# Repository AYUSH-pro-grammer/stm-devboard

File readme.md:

# STM32H573 Development Board

A custom development board based on the STM32H573RIT6 microcontroller, created in KiCad that serves the purpose of learning about the hardware design, PCB layout, power supply and embedded systems.

## Features

### Core components
- Power supply: The board is powered through the USB-C connector. 3.3 V is supplied by the LD1117S33TR regulator.
- Microcontroller: The STM32H573RIT6 processes the firmware code and communicates with peripherals.
- Clock source: 8 MHz crystal serves as an external clock for the microcontroller.
- Pushbuttons and resistors: Used to reset and enter the boot mode.
- USB Protection: USBLC6-2P6 is used for ESD protection of the USB lines.
- Programming and debugging: SWD connector is used for flashing firmware and debugging.
- Headers: Expose some of the pins for expansion.

## The reason behind making this

This board was made by me in order to gain knowledge about how to make an STM32 development board on my own rather than relying on readymade boards available out there.

## Flashing and use

The board is equipped with a USB-C port thus it can be connected to a PC. In case that USB DFU bootloading is set up properly, you may flash the firmware directly via USB and no ST-LINK debugger will be required.

Otherwise, it is still possible to program and debug the board via ST-LINK through the SWD connector.

After flashing the firmware, reboot the board and get started playing around with GPIOs!

## Assembly

The PCB assembly will be done by manually soldering all the parts to the PCB.

## Images

### 3D PCB View — Front

### 3D PCB View — Back

### Schematic

### PCB Routing

## Hardware Design

I have used KiCad to design both the schematic and the PCB.

- `kicad/` — Schematic and PCB design files
- `images/` — Images of PCB rendering, schematic and routing
- `gerber-files/` — PCB manufacturing files
- `bom.csv` — Bill of materials with links to parts
- `grb.zip` — Gerber archive if present

## Bill of Materials

The bill of materials with links to parts is listed in [`bom.csv`](bom.csv)

## BOM

| Qty | Component | Selected Part | Supplier | Link | MOQ | Unit Price (USD) | Order Cost (USD) |
| -------: | ------------- | ----------------- | ------------ | -------- | -------: | --------------------: | -------------------: |
| 100 | 30 pF Capacitor, 0603 C0G | TCC0603COG300J500CT | LCSC | [Link](https://www.lcsc.com/product-detail/C376782.html) | 100 | $0.0042 | $0.42 |
| 20 | Red LED, 0603 | DY-0603SRC-L-SMG | LCSC | [Link](https://www.lcsc.com/product-detail/C524047.html) | 20 | $0.0252 | $0.50 |
| 20 | Schottky Diode, 1N5819 DO-41 | 1N5819 | LCSC | [Link](https://www.lcsc.com/product-detail/C2474.html) | 20 | $0.0367 | $0.73 |
| 10 | 2.2 µF Capacitor, 0805 X7R | CC0805KKX7R7BB225 | LCSC | [Link](https://www.lcsc.com/product-detail/C107128.html) | 10 | $0.0601 | $0.60 |
| 20 | 1 µF Capacitor, 0805 X7R | 0805B105K160CT | LCSC | [Link](https://www.lcsc.com/product-detail/C396719.html) | 20 | $0.0457 | $0.91 |
| 10 | 4.7 µF Capacitor, 0805 X7R | CC0805MKX7R8BB475 | LCSC | [Link](https://www.lcsc.com/product-detail/C5185457.html) | 10 | $0.0717 | $0.72 |
| 50 | 10 pF Capacitor, 0603 NP0 | AC0603JRNPO9BN100 | LCSC | [Link](https://www.lcsc.com/product-detail/C277527.html) | 50 | $0.0106 | $0.53 |
| 5 | 10 µF Capacitor, 0805 X7R | TCC0805X7R106K100FT | LCSC | [Link](https://www.lcsc.com/product-detail/C380346.html) | 5 | $0.0918 | $0.46 |
| 20 | 100 nF Capacitor, 0603 X7R | CC0603JRX7R9BB104 | LCSC | [Link](https://www.lcsc.com/product-detail/C91183.html) | 20 | $0.0209 | $0.42 |
| 50 | Green LED, 0603 | KT-0603G | LCSC | [Link](https://www.lcsc.com/product-detail/C12624.html) | 50 | $0.0124 | $0.62 |
| 50 | Blue LED, 0603 — Backordered | KT-0603B | LCSC | [Link](https://www.lcsc.com/product-detail/C2288.html) | 50 | $0.0104 | $0.52 |
| 1 | USB-C USB 2.0 Connector — Backordered | USB4105-GF-A-060 | LCSC | [Link](https://www.lcsc.com/product-detail/C3025063.html) | 1 | $1.4727 | $1.47 |
| 20 | 1×4 Pin Header, 2.54 mm | PZ254V-11-04P | LCSC | [Link](https://www.lcsc.com/product-detail/C2691448.html) | 20 | $0.0263 | $0.53 |
| 10 | 1×6 Pin Header, 2.54 mm | 2.54-1x6P | LCSC | [Link](https://www.lcsc.com/product-detail/C37208.html) | 10 | $0.0419 | $0.42 |
| 5 | N-Channel MOSFET, SOT-523 | DMG1012T-7 | LCSC | [Link](https://www.lcsc.com/product-detail/C20512.html) | 5 | $0.1019 | $0.51 |
| 20 | 10 kΩ Resistor, 0603 | MCT06030C1002FP500 | LCSC | [Link](https://www.lcsc.com/product-detail/C161803.html) | 20 | $0.0377 | $0.75 |
| 10 | 5.1 kΩ Resistor, 0603 | HoAR0603-1/10W-5.1KR-0.1%-TCR25 | LCSC | [Link](https://www.lcsc.com/product-detail/C5123587.html) | 10 | $0.0728 | $0.73 |
| 20 | 1.4 kΩ Resistor, 0603 | RT0603BRD071K4L | LCSC | [Link](https://www.lcsc.com/product-detail/C705740.html) | 20 | $0.0596 | $1.19 |
| 10 | 1.1 kΩ Resistor, 0603 | RT0603BRD071K1L | LCSC | [Link](https://www.lcsc.com/product-detail/C705736.html) | 10 | $0.0508 | $0.51 |
| 1 | 160 Ω Resistor, 0603 — Backordered | ERJP03F1600V | LCSC | [Link](https://www.lcsc.com/product-detail/C543226.html) | 1 | $0.0598 | $0.06 |
| 1 | 221 Ω Resistor, 0603 — Backordered | ERJ-S03F2210V | LCSC | [Link](https://www.lcsc.com/product-detail/C2113629.html) | 1 | $0.0270 | $0.03 |
| 5 | USB ESD Protection, SOT-666 — Backordered | USBLC6-2P6 | LCSC | [Link](https://www.lcsc.com/product-detail/C15999.html) | 5 | $0.2491 | $1.25 |
| 5 | 3.3 V LDO Regulator, SOT-223 | LD1117S33TR | LCSC | [Link](https://www.lcsc.com/product-detail/C86781.html) | 5 | $0.2467 | $1.23 |
| 5 | 8 MHz Crystal, 18 pF, SMD3225 | 0132M4-8.000F18DTNL | LCSC | [Link](https://www.lcsc.com/product-detail/C51949868.html) | 5 | $0.1920 | $0.96 |
| 1 | STM32H573RIT6 Microcontroller — Backordered | STM32H573RIT6 | LCSC | [Link](https://www.lcsc.com/product-detail/C22371377.html) | 1 | $9.9787 | $9.98 |
| 50 | 6×6 mm Tactile Switch | SH-6X6X5H-STM | LCSC | [Link](https://www.lcsc.com/product-detail/C22383475.html) | 50 | $0.0115 | $0.58 |
| 1 | PCB Fabrication | Custom STM32H573 PCB | JLCPCB | [JLCPCB](https://jlcpcb.com/) | 1 | $8.00 | $8.00 |
| | Total cost | | | | | | $34.63 |

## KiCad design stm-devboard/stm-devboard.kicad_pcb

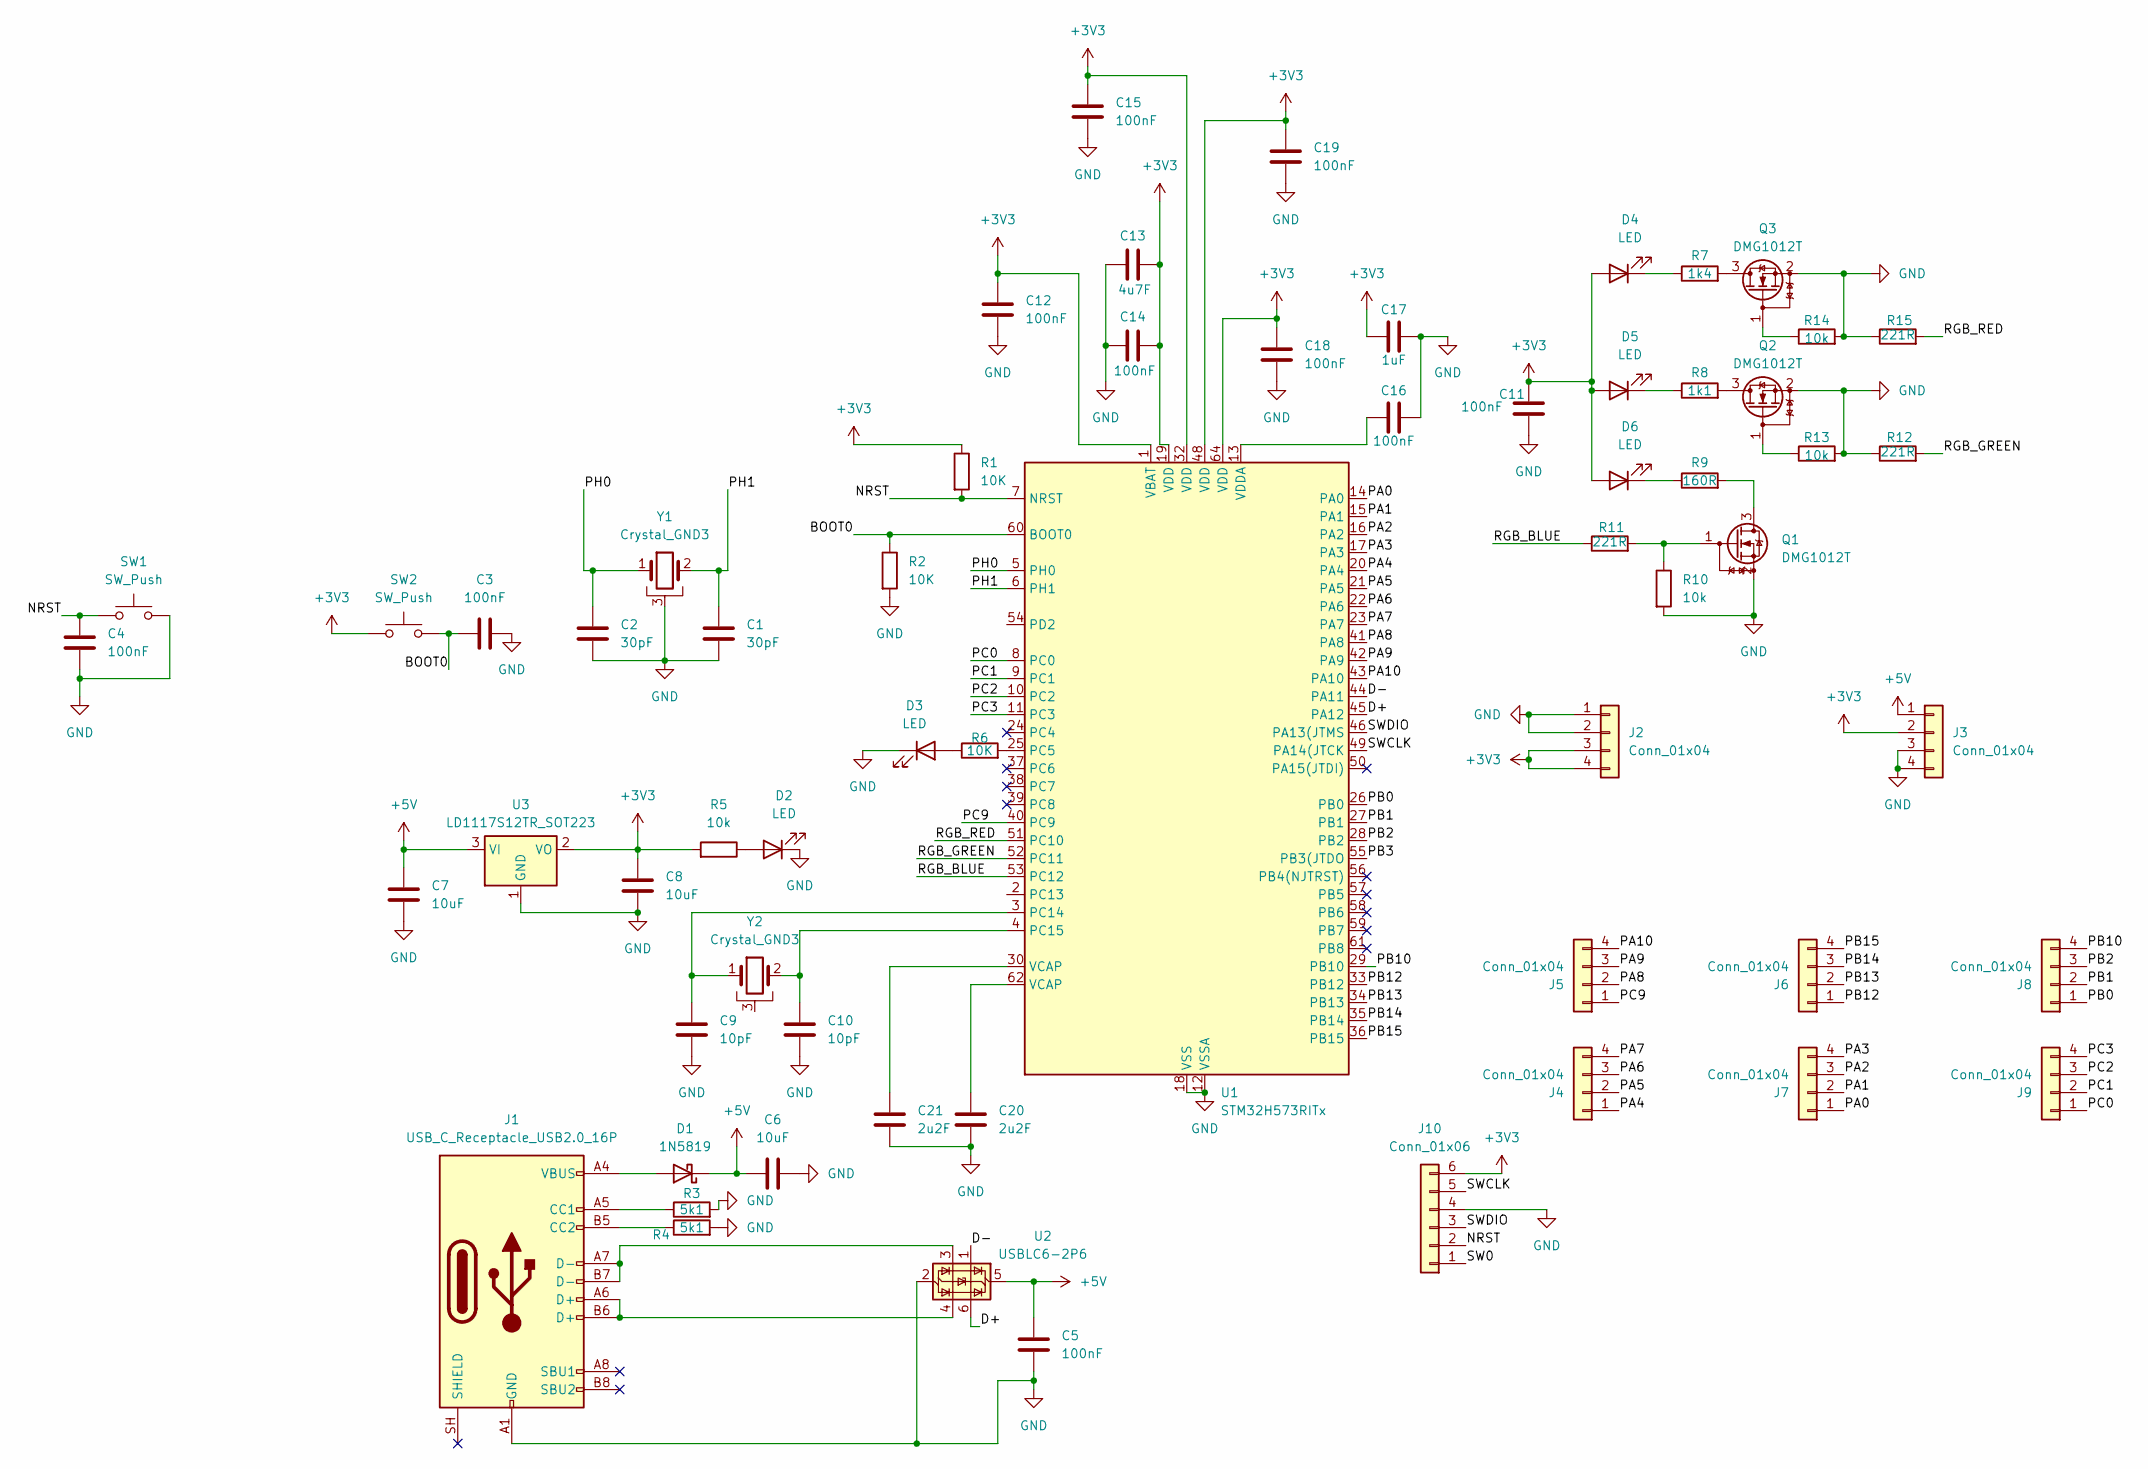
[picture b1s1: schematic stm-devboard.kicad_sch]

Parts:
C1, C2: 30pF; C_0603_1608Metric
C3, C4, C5, C11, C12, C14, C15, C16, C18, C19: 100nF; C_0603_1608Metric
C6, C7, C8: 10uF; C_0805_2012Metric
C9, C10: 10pF; C_0603_1608Metric
C13: 4u7F; C_0805_2012Metric
C17: 1uF; C_0805_2012Metric
C20, C21: 2u2F; C_0805_2012Metric
D1: 1N5819; D_DO-41_SOD81_P10.16mm_Horizontal
D2, D3, D4, D5, D6: LED; LED_0603_1608Metric
J1: USB_C_Receptacle_USB2.0_16P; USB_C_Receptacle_GCT_USB4105-xx-A_16P_TopMnt_Horizontal
J2, J3, J4, J5, J6, J7, J8, J9: Conn_01x04; PinHeader_1x04_P2.54mm_Vertical
J10: Conn_01x06; PinHeader_1x06_P2.54mm_Vertical
Q1, Q2, Q3: DMG1012T; SOT-523
R1, R2, R6: 10K; R_0603_1608Metric
R3, R4: 5k1; R_0603_1608Metric
R5, R10, R13, R14: 10k; R_0603_1608Metric
R7: 1k4; R_0603_1608Metric
R8: 1k1; R_0603_1608Metric
R9: 160R; R_0603_1608Metric
R11, R12, R15: 221R; R_0603_1608Metric
SW1, SW2: SW_Push; SW_PUSH_6mm
U1: STM32H573RITx; LQFP-64_10x10mm_P0.5mm
U2: USBLC6-2P6; SOT-666
U3: LD1117S12TR_SOT223; SOT-223-3_TabPin2
Y1, Y2: Crystal_GND3; Crystal_SMD_3225-4Pin_3.2x2.5mm

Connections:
+3V3: C8.1, C11.1, C12.1, C13.2, C14.2, C15.1, C17.1, C18.1, C19.1, D4.2 (A), D5.2 (A), D6.2 (A), J2.3, J2.4, J3.2, J10.6, R1.1, R5.2, SW2.1, U1.1 (VBAT), U1.19 (VDD), U1.32 (VDD), U1.48 (VDD), U1.64 (VDD), U3.2 (VO)
+5V: C5.1, C6.1, C7.2, D1.1 (K), J3.1, U2.5 (VBUS), U3.3 (VI)
/BOOT0: C3.1, R2.1, SW2.2, U1.60 (BOOT0)
/D+: U1.45 (PA12), U2.6 (I/O1)
/D-: U1.44 (PA11), U2.1 (I/O1)
/NRST: C4.2, J10.2, R1.2, SW1.1, U1.7 (NRST)
/PA0: J7.1, U1.14 (PA0)
/PA1: J7.2, U1.15 (PA1)
/PA2: J7.3, U1.16 (PA2)
/PA3: J7.4, U1.17 (PA3)
/PA4: J4.1, U1.20 (PA4)
/PA5: J4.2, U1.21 (PA5)
/PA6: J4.3, U1.22 (PA6)
/PA7: J4.4, U1.23 (PA7)
/PA8: J5.2, U1.41 (PA8)
/PA9: J5.3, U1.42 (PA9)
/PA10: J5.4, U1.43 (PA10)
/PB0: J8.1, U1.26 (PB0)
/PB1: J8.2, U1.27 (PB1)
/PB2: J8.3, U1.28 (PB2)
/PB3: U1.55 (PB3(JTDO)
/PB10: J8.4, U1.29 (PB10)
/PB12: J6.1, U1.33 (PB12)
/PB13: J6.2, U1.34 (PB13)
/PB14: J6.3, U1.35 (PB14)
/PB15: J6.4, U1.36 (PB15)
/PC0: J9.1, U1.8 (PC0)
/PC1: J9.2, U1.9 (PC1)
/PC2: J9.3, U1.10 (PC2)
/PC3: J9.4, U1.11 (PC3)
/PC9: J5.1, U1.40 (PC9)
/PH0: C2.1, U1.5 (PH0), Y1.1
/PH1: C1.1, U1.6 (PH1), Y1.2
/RGB_BLUE: R11.1, U1.53 (PC12)
/RGB_GREEN: R12.2, U1.52 (PC11)
/RGB_RED: R15.2, U1.51 (PC10)
/SW0: J10.1
/SWCLK: J10.5, U1.49 (PA14(JTCK)
/SWDIO: J10.3, U1.46 (PA13(JTMS)
unnamed: C20.1, U1.62 (VCAP)
unnamed: C21.1, U1.30 (VCAP)
unnamed: D1.2 (A), J1.A4 (VBUS), J1.A9 (VBUS), J1.B4 (VBUS), J1.B9 (VBUS)
unnamed: D2.2 (A), R5.1
unnamed: D3.2 (A), R6.1
unnamed: D4.1 (K), R7.1
unnamed: D5.1 (K), R8.1
unnamed: D6.1 (K), R9.1
unnamed: J1.A5 (CC1), R3.1
unnamed: J1.B5 (CC2), R4.1
unnamed: J1.A6 (D+), J1.B6 (D+), U2.4 (I/O2)
unnamed: J1.A7 (D-), J1.B7 (D-), U2.3 (I/O2)
unnamed: Q1.3 (D), R9.2
unnamed: Q1.1 (G), R10.1, R11.2
unnamed: Q2.3 (D), R8.2
unnamed: Q3.3 (D), R7.2
unnamed: R6.2, U1.25 (PC5)
unnamed: C9.1, U1.3 (PC14), Y2.1
unnamed: C10.1, U1.4 (PC15), Y2.2
unnamed: C16.1, U1.13 (VDDA)

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
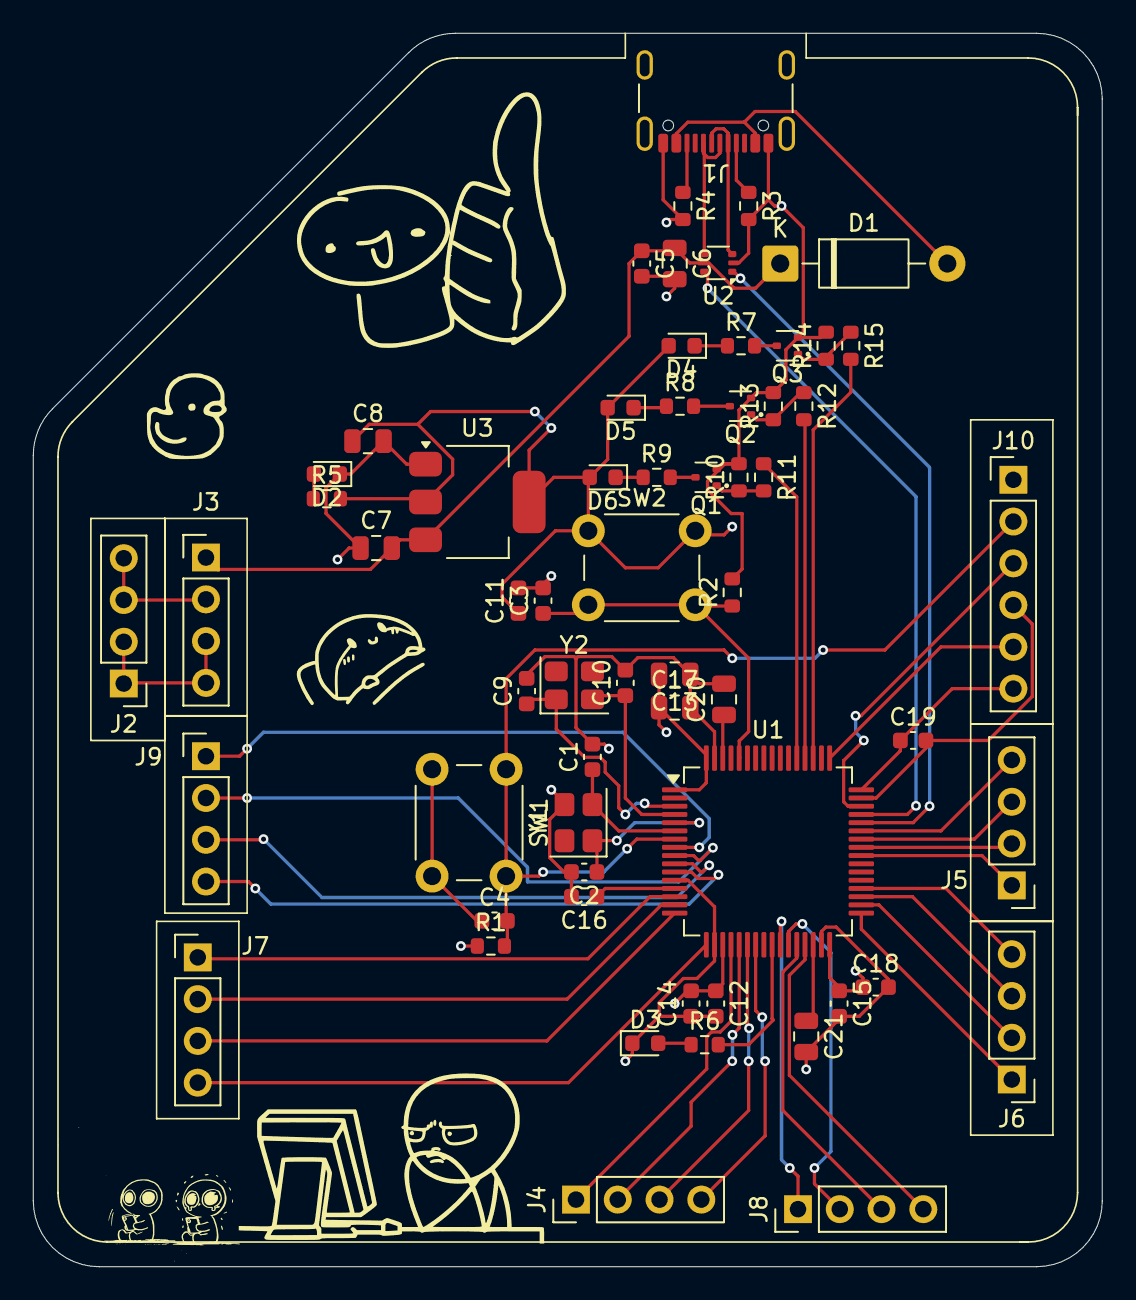
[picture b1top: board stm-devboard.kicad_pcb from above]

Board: 4 copper layers, 65.0 x 75.0 mm, 62 parts (0 on the bottom side), 60 nets.
